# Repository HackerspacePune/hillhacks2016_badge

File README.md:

PCB badge for hillhacks.in
==========================

Designed in kicad 4.0.2

Based on Adafruit trinket and Digispark designs. Can use either Adafruit's 
trinket/gemma bootloader, or micronucleus(which digispark uses).
Reverse protection for USB and battery with schottky diodes(and supply 
selection also), no voltage regulator, Zener diodes are to clip D+/D- 
voltage level to within USB spec. 1.5k on D- is part of USB spec's Low 
speed USB detection.

Hillhacks logo is from header on site.

Design uses a footprint(pcb_USB-A) from Inversepath's Usbarmory kicad design https://github.com/inversepath/usbarmory/

Firmware
========

Bootloader: Please follow [these instructions](https://learn.adafruit.com/introducing-trinket/repairing-bootloader) for
installing Adafruit Trinket bootloader onto your badge. This allows you to upload 'sletches' to the badge without an external programmer.

Arduino IDE: Set up arduino IDE to work with your badge from [here](https://learn.adafruit.com/introducing-trinket/setting-up-with-arduino-ide).

Hardware
========

Please see [Schematic.pdf](Schematic.pdf) for schematic. Pin PB0(D0 for arduino) is
connected to push button. PB1(D1) is connected to LED.

NOTE: The button footprint is rotated by 90 degrees by mistake, so you need to bend the button
leads so they can be fit the PCB roated. 

NOTE2: the battery holder pins need to be bent out a bit
to fit the PCB.

Example code
============

Please see [/examples/HillhacksBadge.ino](/examples/HillhacksBadge.ino) for Mitch's example sketch.

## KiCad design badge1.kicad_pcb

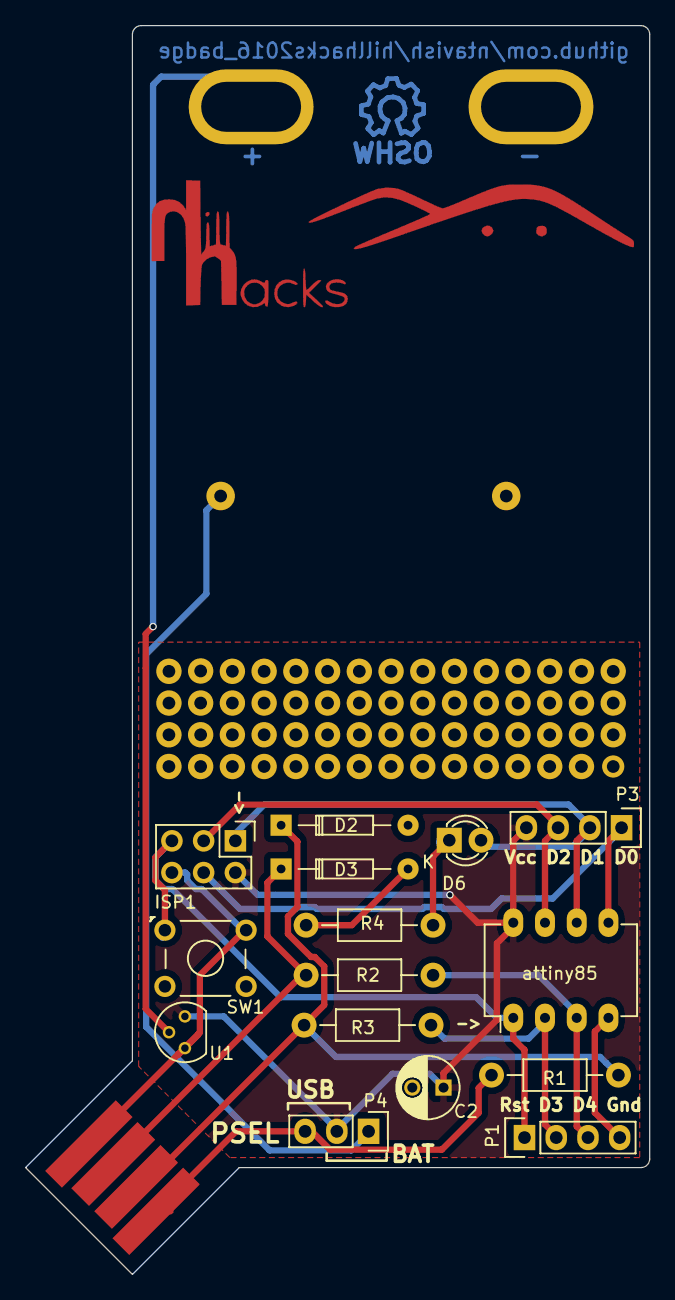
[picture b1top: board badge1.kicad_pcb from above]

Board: 2 copper layers, 50.0 x 100.0 mm, 23 parts (1 on the bottom side), 14 nets.

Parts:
BT1: Battery; CR2032H
C2: 4.7uF; C_Radial_D5_L11_P2.5
D2, D3: 3.6V BZX79C3V6; Diode_DO-35_SOD27_Horizontal_RM10
D6: LED; LED-3MM
ISP1: AVR-ISP-6; Pin_Header_Straight_2x03
P1, P3: CONN_01X04; Pin_Header_Straight_1x04
P2: USB_A; usb-PCB
P4: CONN_01X03; Pin_Header_Straight_1x03
R1: 1.5k; Resistor_Horizontal_RM10mm
R2, R3: 68; Resistor_Horizontal_RM10mm
R4: 470; Resistor_Horizontal_RM10mm
SW1: SW_PUSH; OPL_DIP_BUTTON_TS-1109_BEST_SHENZEN
U1: MCP1700-3302E/TO; TO-92_Molded_Narrow
U2: custom_logo; Symbol_OSHW-Logo_CopperBottom
U3: Hillhacks_logo; hh_logo
U4: proto_area
U5, U6: badge_hole2; badge_hole_6mmx3mm(+2mmCu)
U7: custom_logo; tesseract
attiny85: ATTINY85-S; DIP-8_W7.62mm_LongPads

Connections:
/D0: ISP1.4, P3.1, attiny85.5
/D1: D6.2, ISP1.1, P3.2, attiny85.6
/D2: ISP1.3, P3.3, attiny85.7
/D3: P1.2, R3.2, attiny85.2
/D4: P1.3, R2.2, attiny85.3
/RST: ISP1.5, P1.1, SW1.1, attiny85.1
/USB-D+: D3.1, P2.3, R2.1
/USB-D-: D2.1, P2.2, R1.1, R3.1
/VBAT: BT1.1, P4.1
/VBUS: P2.1, P4.3, R1.2
/V_sec_bat: U1.2, U5.1
GND: BT1.2, C2.2, D2.2, D3.2, ISP1.6, P1.4, P2.4, R4.2, SW1.2, U1.1, U6.1, attiny85.4
unnamed: D6.1, R4.1
VCC: C2.1, ISP1.2, P3.4, P4.2, U1.3, attiny85.8

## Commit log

2016-03-02 initial release
2016-03-03 Updated with @anool's comments.
2016-03-09 added tessearact logo. smoothed 3 corners.
2016-03-09 hide U4
2016-03-09 fixed positions of silkscreen texts, tesseract logo to F.Mask
2016-03-12 minor changes. increase via size. update rendering with colour.
2016-03-12 added OPL button footprint
2016-04-07 fixed mistakes and made button the reset button. added more legend.
2016-04-10 Update schematic/layout with fixes. Update readme for small howto.
2016-04-12 minor
2016-05-28 Updated documentation
